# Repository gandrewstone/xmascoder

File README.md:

# xmascoder
Christmas LED light string hardware and software

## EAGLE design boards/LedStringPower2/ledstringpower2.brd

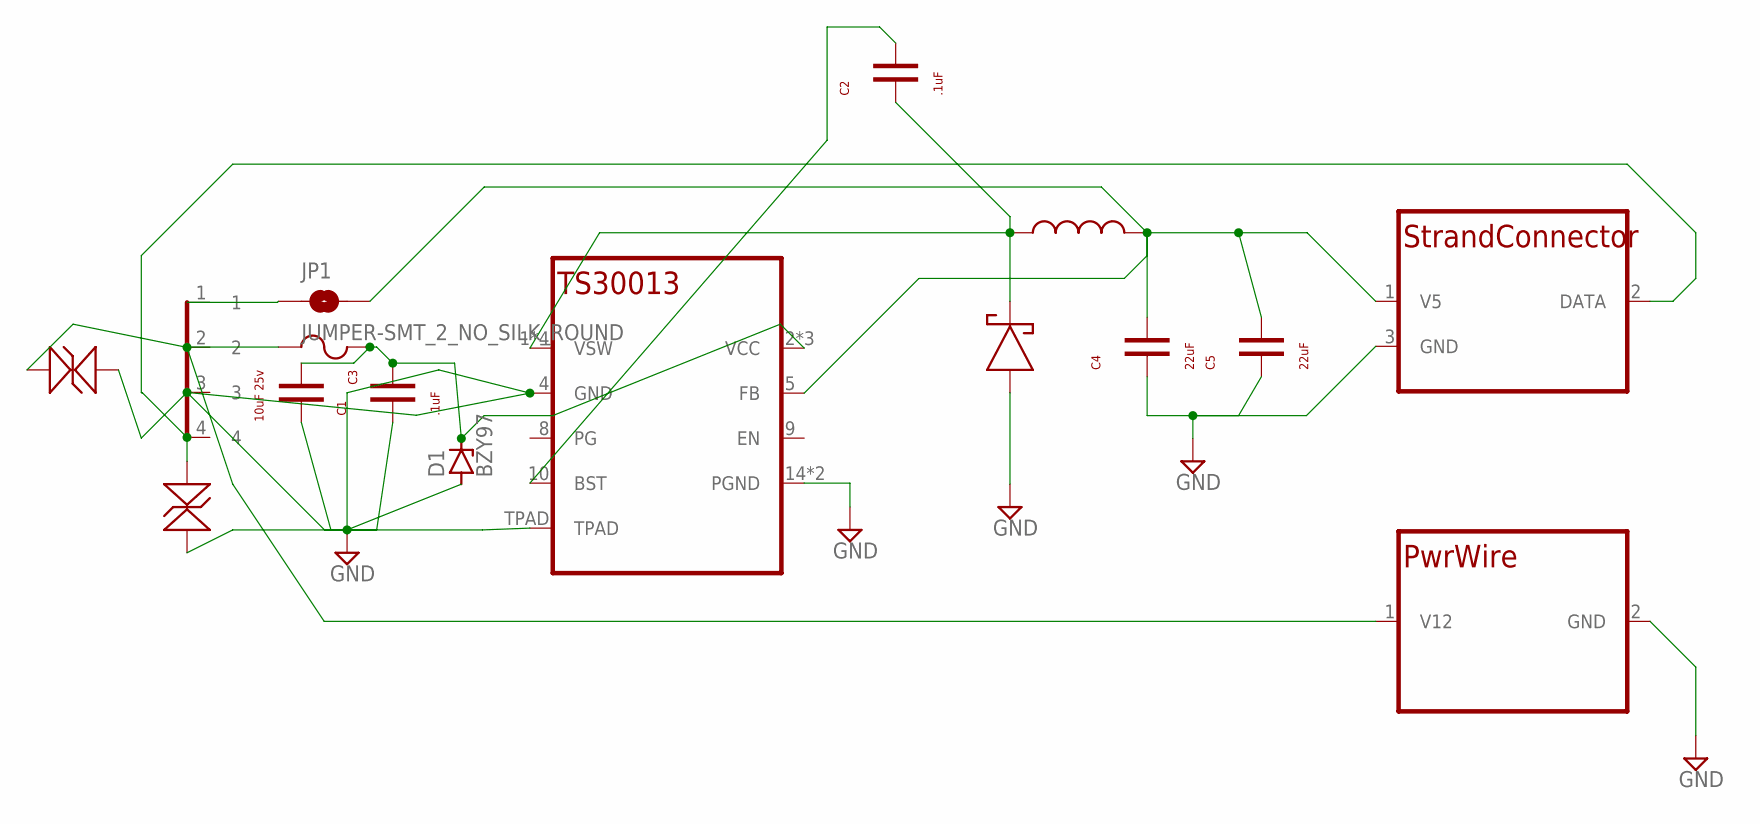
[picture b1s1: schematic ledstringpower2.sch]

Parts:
C1, C2: .1uF; C0603
C3: 10uF 25v; C1206
C4, C5: 22uF; C0603
D1: BZY97; F126Z12
D2: LS54LS54; LS54
F1: 3A; R0603
IC1: TS30013QFN16; QFN16
JP1: JUMPER-SMT_2_NO_SILK_ROUND; SMT-JUMPER_2_NO_SILK_ROUND
L1: SRN5040TA-4R7MSRN5040TA; SRN5040TA
TVS1, TVS2: DESD5V0U1BL-7BDFN1006-2; DFN1006-2
U$3: TE-1969806-1TE-1969806-1; TE-1969806-1
U$5: LEDSTRANDDLEDWIREP; LEDWIREP
U$8: PWRWIREDPWRWIREP; PWRWIREP

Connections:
DATA: TVS2.2, U$3.4, U$5.2 (DATA)
GND: C1.1, C3.2, C4.1, C5.1, D1.A, D2.1, IC1.4 (GND), IC1.14 (PGND), IC1.15 (PGND), IC1.TPAD, TVS1.1, TVS2.1, U$3.3, U$5.3 (GND), U$8.2 (GND)
unnamed: C2.1, D2.2, IC1.1 (VSW), IC1.12 (VSW), IC1.13 (VSW), IC1.16 (VSW), L1.1
unnamed: C2.2, IC1.10 (BST)
unnamed: JP1.1, U$3.1
V5: C4.2, C5.2, IC1.5 (FB), JP1.2, L1.2, U$5.1 (V5)
V12: F1.1, TVS1.2, U$3.2, U$8.1 (V12)
VCC: C1.2, C3.1, D1.C, F1.2, IC1.2 (VCC), IC1.3 (VCC), IC1.11 (VCC)

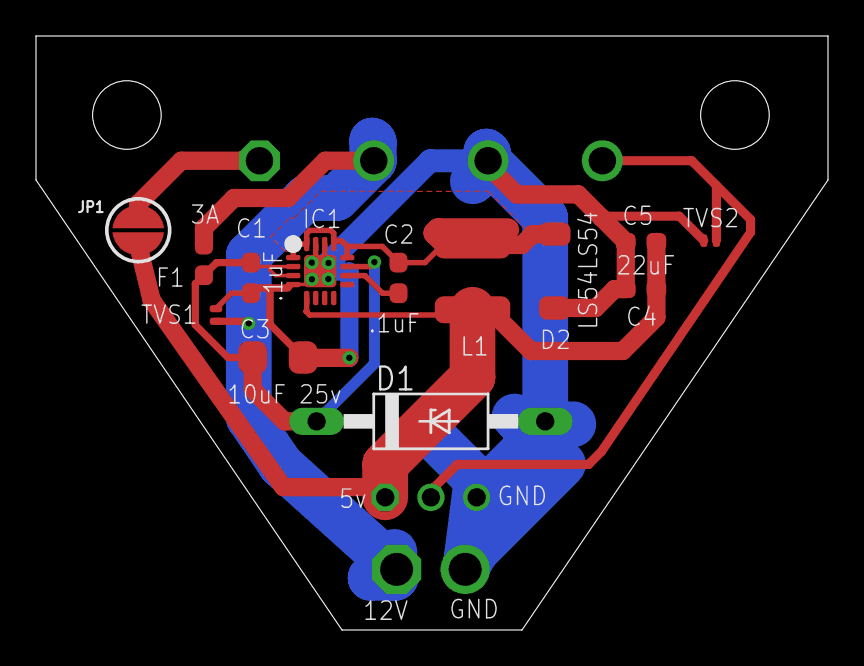
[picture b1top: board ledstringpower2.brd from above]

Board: 2 copper layers, 44.0 x 33.0 mm, 16 parts (0 on the bottom side), 8 nets.

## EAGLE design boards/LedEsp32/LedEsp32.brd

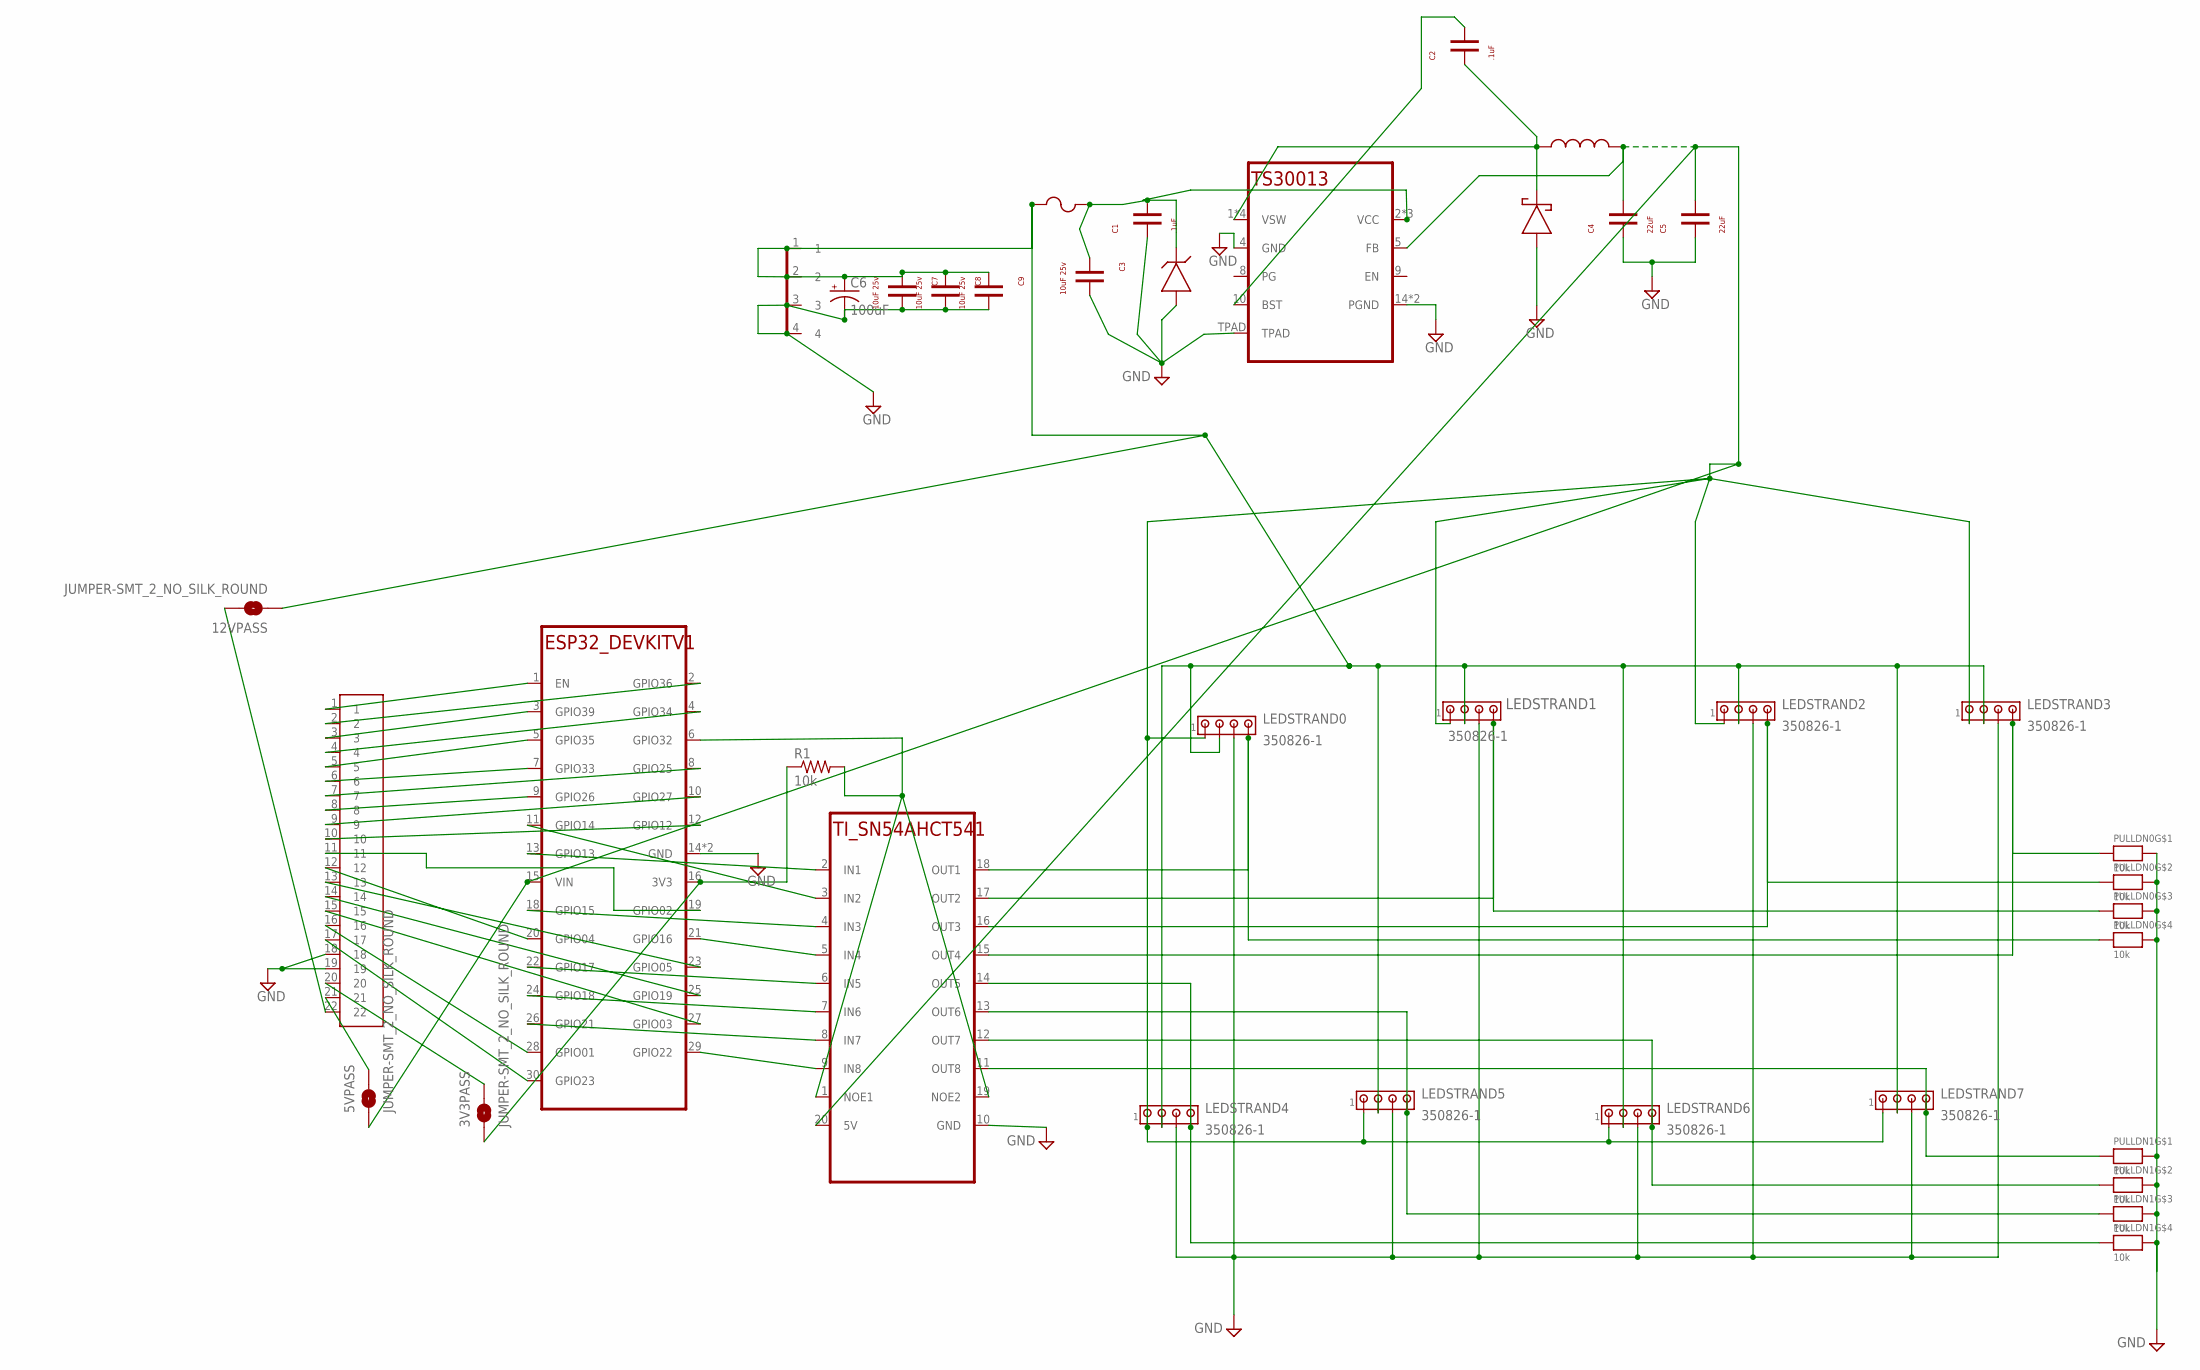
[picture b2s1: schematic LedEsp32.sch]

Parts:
3V3PASS, 5VPASS, 12VPASS: JUMPER-SMT_2_NO_SILK_ROUND; SMT-JUMPER_2_NO_SILK_ROUND
C1, C2: .1uF; C0603
C3, C7, C8, C9: 10uF 25v; C1206
C4, C5: 22uF; C0603
C6: 100uF; E2,5-6
D2: LS54LS54; LS54
F1: 3A; R0603
IC1: TS30013QFN16; QFN16
L1: SRN5040TA-4R7MSRN5040TA; SRN5040TA
LEDSTRAND0, LEDSTRAND1, LEDSTRAND2, LEDSTRAND3, LEDSTRAND4, LEDSTRAND5, LEDSTRAND6, LEDSTRAND7: 350826-1
PULLDN0, PULLDN1: 10k; RESPACK_4X0603
R1: 10k; R0603
U$1: ESP32_DEVKITV1ESP32_DEVKITV1DEVINST; ESP32_DEVKITV1
U$2: TI_SN54AHCT541SO20WDEVINST; SO20W
U$3: 1X22THM; 1X22
U$4: TE-1969806-1TE-1969806-1DEVINST; TE-1969806-1
Z1: CZRB5353B-HF DO-214AADEVINST; DO-214AA

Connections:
3V3: 3V3PASS.1, R1.1, U$1.16 (3V3)
3V3PASS: 3V3PASS.2, U$3.20
GND: C1.1, C3.2, C4.1, C5.1, C6.-, C7.2, C8.2, C9.2, D2.1, IC1.4 (GND), IC1.14 (PGND), IC1.15 (PGND), IC1.TPAD, LEDSTRAND0.3, LEDSTRAND1.3, LEDSTRAND2.3, LEDSTRAND3.3, LEDSTRAND4.3, LEDSTRAND5.3, LEDSTRAND6.3, LEDSTRAND7.3, PULLDN0.5 (2), PULLDN0.6 (2), PULLDN0.7 (2), PULLDN0.8 (2), PULLDN1.5 (2), PULLDN1.6 (2), PULLDN1.7 (2), PULLDN1.8 (2), U$1.14 (GND), U$1.17 (GND), U$2.10 (GND), U$3.18, U$3.19, U$4.3, U$4.4, Z1.1
LEDEN: R1.2, U$1.6 (GPIO32), U$2.1 (NOE1), U$2.19 (NOE2)
unnamed: LEDSTRAND0.4, PULLDN0.4 (1), U$2.18 (OUT1)
unnamed: U$1.19 (GPIO02), U$3.11
unnamed: C2.1, D2.2, IC1.1 (VSW), IC1.12 (VSW), IC1.13 (VSW), IC1.16 (VSW), L1.1
unnamed: C2.2, IC1.10 (BST)
unnamed: LEDSTRAND1.4, PULLDN0.3 (1), U$2.17 (OUT2)
unnamed: LEDSTRAND2.4, PULLDN0.2 (1), U$2.16 (OUT3)
unnamed: LEDSTRAND3.4, PULLDN0.1, U$2.15 (OUT4)
unnamed: LEDSTRAND4.4, PULLDN1.4 (1), U$2.14 (OUT5)
unnamed: LEDSTRAND5.4, PULLDN1.3 (1), U$2.13 (OUT6)
unnamed: LEDSTRAND6.4, PULLDN1.2 (1), U$2.12 (OUT7)
unnamed: LEDSTRAND7.4, PULLDN1.1, U$2.11 (OUT8)
unnamed: U$1.11 (GPIO14), U$2.3 (IN2)
unnamed: U$1.13 (GPIO13), U$2.2 (IN1)
unnamed: U$1.18 (GPIO15), U$2.4 (IN3)
unnamed: U$1.21 (GPIO16), U$2.5 (IN4)
unnamed: U$1.22 (GPIO17), U$2.6 (IN5)
unnamed: U$1.24 (GPIO18), U$2.7 (IN6)
unnamed: U$1.26 (GPIO21), U$2.8 (IN7)
unnamed: U$1.29 (GPIO22), U$2.9 (IN8)
unnamed: U$1.1 (EN), U$3.1
unnamed: U$1.2 (GPIO36), U$3.2
unnamed: U$1.3 (GPIO39), U$3.3
unnamed: U$1.4 (GPIO34), U$3.4
unnamed: U$1.5 (GPIO35), U$3.5
unnamed: U$1.7 (GPIO33), U$3.6
unnamed: U$1.8 (GPIO25), U$3.7
unnamed: U$1.9 (GPIO26), U$3.8
unnamed: U$1.10 (GPIO27), U$3.9
unnamed: U$1.12 (GPIO12), U$3.10
unnamed: U$1.20 (GPIO04), U$3.12
unnamed: U$1.23 (GPIO05), U$3.13
unnamed: U$1.25 (GPIO19), U$3.14
unnamed: U$1.27 (GPIO03), U$3.15
unnamed: U$1.28 (GPIO01), U$3.16
unnamed: U$1.30 (GPIO23), U$3.17
unnamed: 5VPASS.2, U$3.21
unnamed: 12VPASS.2, U$3.22
V5: 5VPASS.1, C4.2, C5.2, IC1.5 (FB), L1.2, LEDSTRAND0.1, LEDSTRAND1.1, LEDSTRAND2.1, LEDSTRAND3.1, LEDSTRAND4.1, LEDSTRAND5.1, LEDSTRAND6.1, LEDSTRAND7.1, U$1.15 (VIN), U$2.20 (5V)
V12_FUSED: C1.2, C3.1, F1.2, IC1.2 (VCC), IC1.3 (VCC), IC1.11 (VCC), Z1.2
VCC: 12VPASS.1, C6.+, C7.1, C8.1, C9.1, F1.1, LEDSTRAND0.2, LEDSTRAND1.2, LEDSTRAND2.2, LEDSTRAND3.2, LEDSTRAND4.2, LEDSTRAND5.2, LEDSTRAND6.2, LEDSTRAND7.2, U$4.1, U$4.2

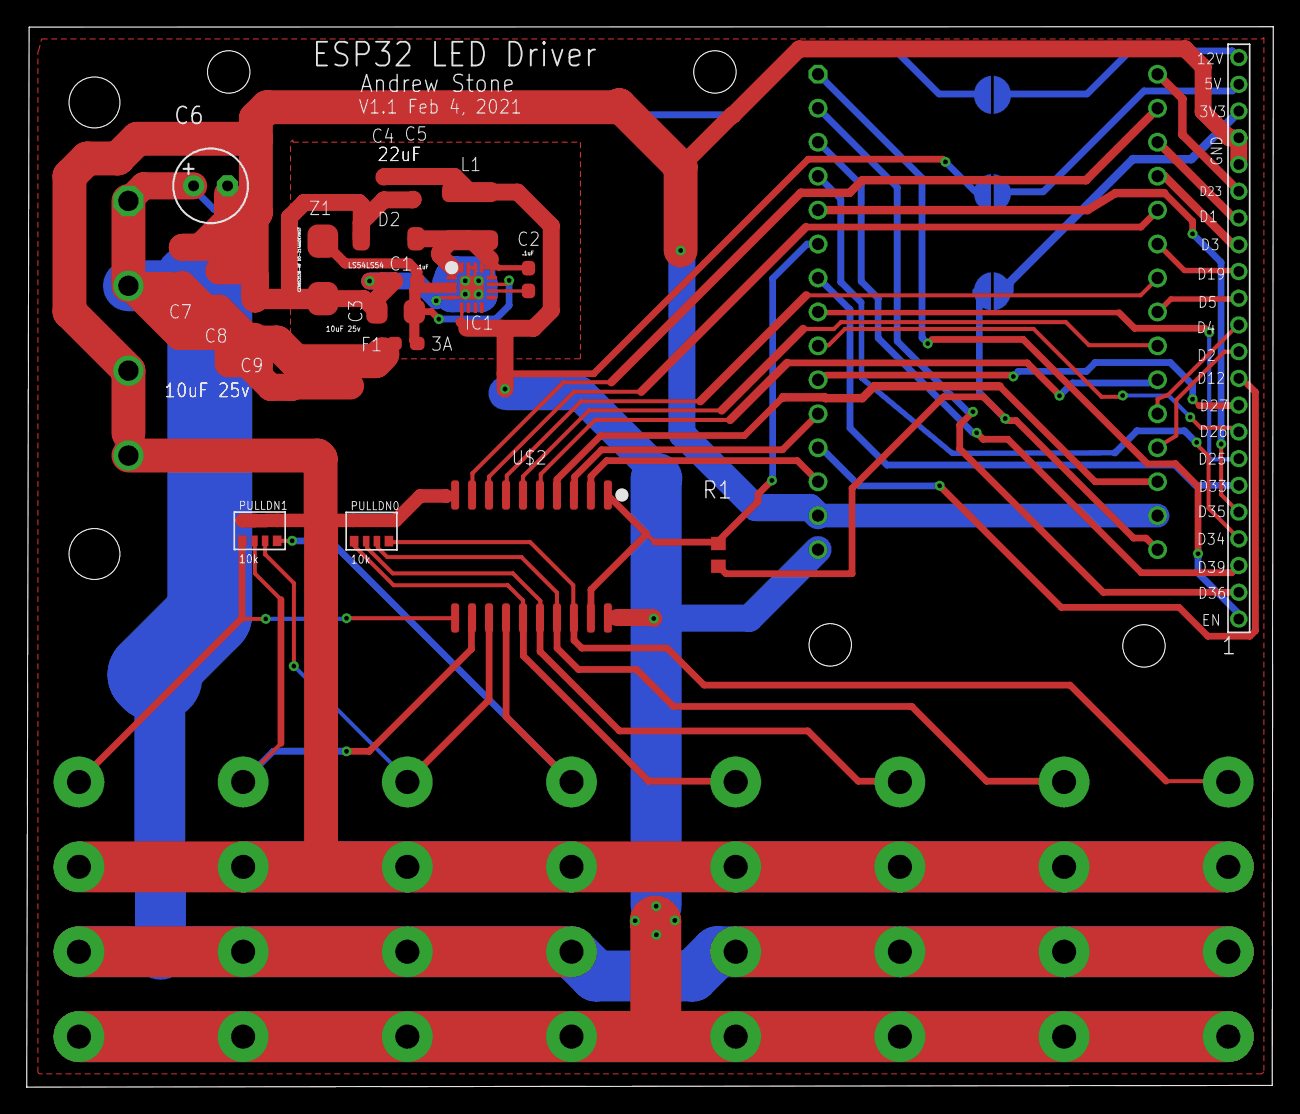
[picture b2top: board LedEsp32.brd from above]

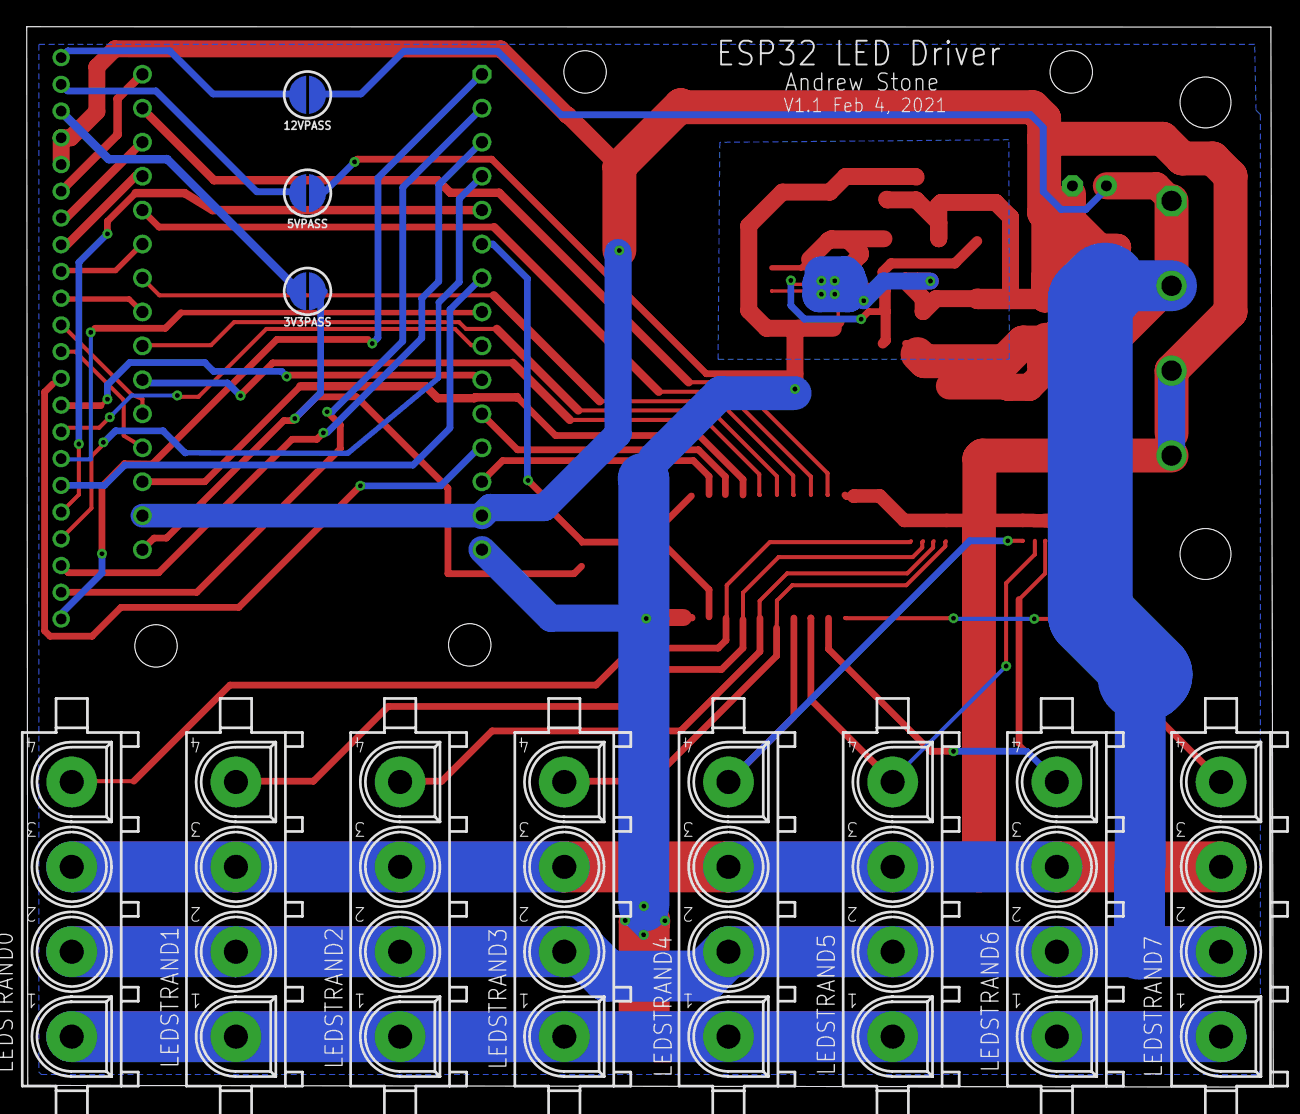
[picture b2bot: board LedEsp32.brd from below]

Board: 2 copper layers, 93.3 x 79.3 mm, 32 parts (12 on the bottom side), 44 nets.

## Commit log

2021-12-03 2021
2023-12-20 fixes in 2022
2023-12-20 trigger the patterns off of the global time so that if this time is synced, the patterns will be
2023-12-20 make wifi search work alongside default pattern

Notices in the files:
parts and their libraries:
SparkFun-Jumpers: Licensing: Creative Commons ShareAlike 4.0 International - https://creativecommons.org/licenses/by-sa/4.0
